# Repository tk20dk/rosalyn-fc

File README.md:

# rosalyn-fc
Rosalyn fligth controller

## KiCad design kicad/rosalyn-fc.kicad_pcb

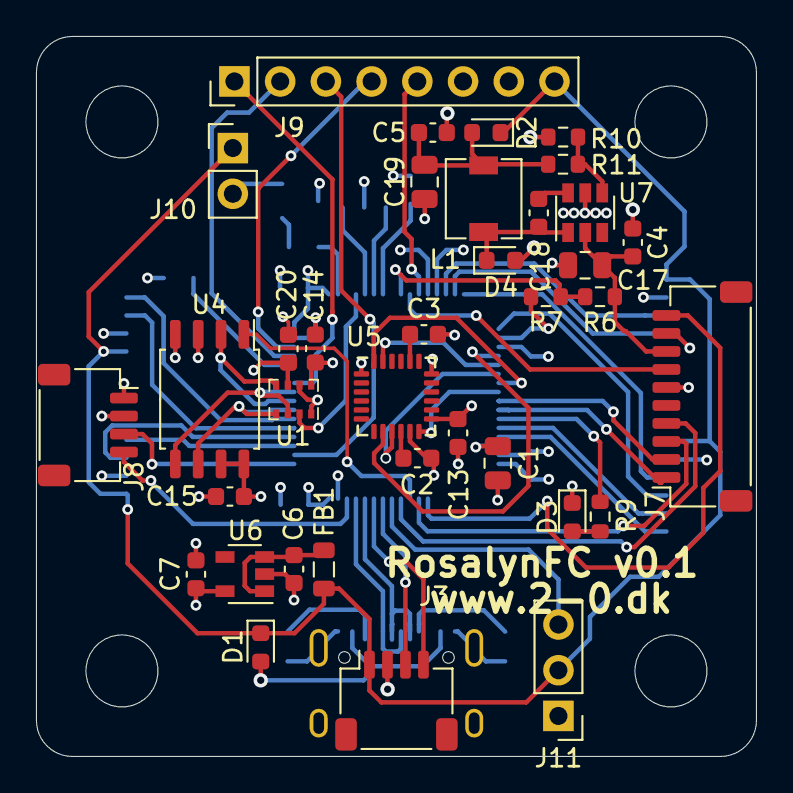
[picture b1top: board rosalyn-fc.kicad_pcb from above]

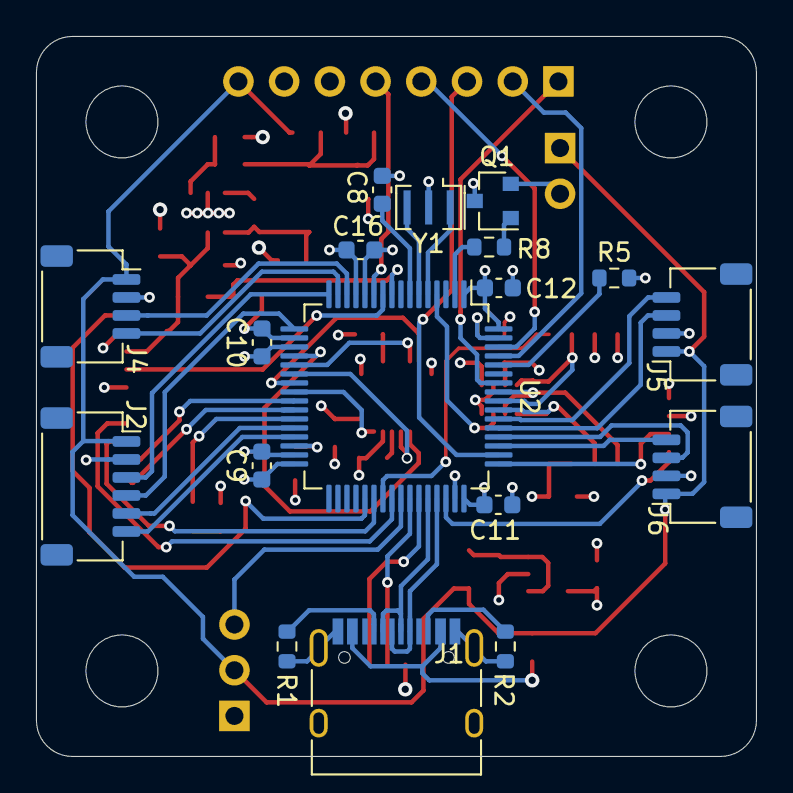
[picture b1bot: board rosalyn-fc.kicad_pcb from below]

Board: 4 copper layers, 40.0 x 40.0 mm, 58 parts (18 on the bottom side), 63 nets.

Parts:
C1: 4u7; C_0805_2012Metric
C2, C4, C5, C8, C9, C10, C11, C12, C13, C14, C15, C16, C20: 100n; C_0603_1608Metric
C3: 2.2n; C_0603_1608Metric
C6, C7: 1u; C_0603_1608Metric
C17: 10u; C_0805_2012Metric
C18: 22n; C_0603_1608Metric
C19: 22u; C_0805_2012Metric
D1, D2: D_Schottky; D_0603_1608Metric
D3: LED; LED_0603_1608Metric
D4: 1n5819; D_0603_1608Metric
FB1: Ferrite_Bead; L_0805_2012Metric
H1, H2, H3, H4: MountingHole; MountingHole_4mm
J1: USB-C; USB_C_Receptacle_HRO_TYPE-C-31-M-12
J2: GPS/MAG; JST_SH_SM06B-SRSS-TB_1x06-1MP_P1.00mm_Horizontal
J3: Terminal; JST_SH_SM04B-SRSS-TB_1x04-1MP_P1.00mm_Horizontal
J4: Satellite; JST_SH_SM04B-SRSS-TB_1x04-1MP_P1.00mm_Horizontal
J5: Serial1; JST_SH_SM04B-SRSS-TB_1x04-1MP_P1.00mm_Horizontal
J6: Serial2; JST_SH_SM04B-SRSS-TB_1x04-1MP_P1.00mm_Horizontal
J7: ESC; JST_SH_SM10B-SRSS-TB_1x10-1MP_P1.00mm_Horizontal
J8: SWD; JST_SH_SM04B-SRSS-TB_1x04-1MP_P1.00mm_Horizontal
J9: Expansion; PinHeader_1x08_P2.54mm_Vertical
J10: Buzzer; PinHeader_1x02_P2.54mm_Vertical
J11: PWM_LED; PinHeader_1x03_P2.54mm_Vertical
L1: 4,7u; L_4.1x4.1_H1.75
Q1: Q_NPN_BCE; SOT-23
R1, R2: 5k1; R_0603_1608Metric
R5: 100k; R_0603_1608Metric
R6: 10k; R_0603_1608Metric
R7: 1k; R_0603_1608Metric
R8, R9: R; R_0603_1608Metric
R10: 49,9k; R_0603_1608Metric
R11: 9,53k; R_0603_1608Metric
U1: BMP280; Bosch_LGA-8_2x2.5mm_P0.65mm_ClockwisePinNumbering
U2: STM32F722RETx; LQFP-64_10x10mm_P0.5mm
U4: W25Q128JVS; SOIC-8_5.275x5.275mm_P1.27mm
U5: MPU-6000; InvenSense_QFN-24_4x4mm_P0.5mm
U6: LP2985-3.3; SOT-23-5
U7: ACT4088; SOT-23-6
Y1: 8MHz; Resonator_SMD_muRata_CSTxExxV-3Pin_3.0x1.1mm

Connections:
+3V3: C7.1, C9.1, C10.1, C11.1, C12.1, C13.1, C14.1, C15.1, C16.1, C20.1, D3.1, J8.1, J9.7, U1.6, U1.8, U2.1, U2.13, U2.19, U2.32, U2.48, U2.64, U4.3, U4.7, U4.8, U5.13, U6.5
+5V: D1.1, D2.1, FB1.2, J2.1, J3.1, J4.1, J5.1, J6.1, J9.8, J10.1, J11.2
GND: C1.1, C2.2, C3.2, C4.2, C5.2, C6.1, C7.2, C8.2, C9.2, C10.2, C11.2, C12.2, C13.2, C14.2, C15.2, C16.2, C17.1, C19.2, C20.2, D4.2, J1.A1, J1.A12, J1.B1, J1.B12, J1.S1, J2.2, J3.2, J4.2, J5.2, J6.2, J7.6, J7.9, J8.2, J9.6, J11.1, Q1.3, R1.1, R2.1, R5.2, R7.2, R11.2, U1.1, U1.7, U2.12, U2.18, U2.31, U2.47, U2.63, U4.4, U5.1, U5.11, U5.18, U6.2, U7.5, Y1.2
unnamed: C1.2, U2.30
unnamed: C2.1, U5.10
unnamed: C3.1, U5.20
unnamed: C6.2, FB1.1, U6.1, U6.3
unnamed: C18.1, U7.6
unnamed: C18.2, D4.1, L1.2, U7.1
unnamed: C5.1, C19.1, D2.2, L1.1, R10.1
unnamed: D1.2, J1.A4, J1.A9, J1.B4, J1.B9
unnamed: D3.2, R9.2
unnamed: J1.A5, R1.2
unnamed: J1.B5, R2.2
unnamed: J10.2, Q1.2
unnamed: Q1.1, R8.1
unnamed: R10.2, R11.1, U7.4
unnamed: U2.5, Y1.1
unnamed: U2.6, Y1.3
baro_cs: U1.2, U2.4
beeper: R8.2, U2.2
boot0: R5.1, U2.60
camera: J9.4, U2.62
current_adc: J7.7, U2.10
flash_cs: U2.39, U4.1
gyro1_cs: U2.20, U5.8
gyro1_exti: U2.24, U5.12
i2c2_scl: J2.5, U2.28
i2c2_sda: J2.6, U2.29
led: J11.3, U2.41
led0: R9.1, U2.27
m1: J7.4, U2.40
m2: J7.3, U2.38
m3: J7.2, U2.25
m4: J7.1, U2.26
m5: J9.1, U2.58
m6: J9.2, U2.61
nrst: C8.1, U2.7
ppm: J9.3, U2.50
rssi_adc: J9.5, U2.11
spi1_miso: U2.22, U5.9
spi1_mosi: U2.23, U5.24
spi1_sck: U2.21, U5.23
spi3_miso: U1.5, U2.56, U4.2
spi3_mosi: U1.3, U2.57, U4.5
spi3_sck: U1.4, U2.55, U4.6
swclk: J8.3, U2.49
swdio: J8.4, U2.46
uart4_rx: J4.4, U2.15
uart4_tx: J4.3, U2.14
uart5_rx: J5.4, U2.54
uart5_tx: J5.3, U2.53
uart6_rxtx: J7.10, U2.37
usart1_rx: J3.4, U2.43
usart1_tx: J3.3, U2.42
usart2_rx: J2.4, U2.17
usart2_tx: J2.3, U2.16
usart3_rx: J6.4, U2.51
usart3_tx: J6.3, U2.52
usb_dm: J1.A7, J1.B7, U2.44
usb_dp: J1.A6, J1.B6, U2.45
vbat: C4.1, C17.2, J7.8, R6.1, U7.2
vbat_adc: R6.2, R7.1, U2.9

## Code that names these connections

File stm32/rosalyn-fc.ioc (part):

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Mcu.Name=STM32F722R(C-E)Tx
Mcu.Package=LQFP64
Mcu.UserName=STM32F722RETx
PA0-WKUP.Mode=Asynchronous
PA0-WKUP.Signal=UART4_TX
PA1.Mode=Asynchronous
PA1.Signal=UART4_RX
PA10.Mode=Asynchronous
PA10.Signal=USART1_RX
PA11.Mode=Device_Only
PA11.Signal=USB_OTG_FS_DM
PA12.Mode=Device_Only
PA12.Signal=USB_OTG_FS_DP
PA13.Mode=Serial_Wire
PA13.Signal=SYS_JTMS-SWDIO
PA14.Mode=Serial_Wire
PA14.Signal=SYS_JTCK-SWCLK
PA15.GPIOParameters=GPIO_Label
PA15.GPIO_Label=PPM
PA15.Signal=S_TIM2_CH1_ETR
PA2.Mode=Asynchronous
PA2.Signal=USART2_TX
PA3.Mode=Asynchronous
PA3.Signal=USART2_RX
PA4.GPIOParameters=PinState,GPIO_Label
PA4.GPIO_Label=GYRO1_NSS
PA4.PinState=GPIO_PIN_SET
PA4.Signal=GPIO_Output
PA5.Mode=Full_Duplex_Master
PA5.Signal=SPI1_SCK
PA6.GPIOParameters=GPIO_PuPd
PA6.GPIO_PuPd=GPIO_PULLUP
PA6.Mode=Full_Duplex_Master
PA6.Signal=SPI1_MISO
PA7.Mode=Full_Duplex_Master
PA7.Signal=SPI1_MOSI
PA8.GPIOParameters=GPIO_Label
PA8.GPIO_Label=LED
PA8.Signal=S_TIM1_CH1
PA9.Mode=Asynchronous
PA9.Signal=USART1_TX
PB0.GPIOParameters=GPIO_Label
PB0.GPIO_Label=M3
PB0.Signal=S_TIM3_CH3
PB1.GPIOParameters=GPIO_Label
PB1.GPIO_Label=M4
PB1.Signal=S_TIM3_CH4
PB10.Mode=I2C
PB10.Signal=I2C2_SCL
PB11.Mode=I2C
PB11.Signal=I2C2_SDA
PB12.GPIOParameters=PinState,GPIO_Label
PB12.GPIO_Label=SPI2_NSS
PB12.PinState=GPIO_PIN_SET
PB12.Signal=GPIO_Output
PB13.Mode=Full_Duplex_Master
PB13.Signal=SPI2_SCK
PB14.GPIOParameters=GPIO_PuPd
PB14.GPIO_PuPd=GPIO_PULLUP
PB14.Mode=Full_Duplex_Master
PB14.Signal=SPI2_MISO
PB15.Mode=Full_Duplex_Master
PB15.Signal=SPI2_MOSI
PB2.GPIOParameters=PinState,GPIO_Label
PB2.GPIO_Label=LED0
PB2.PinState=GPIO_PIN_SET
PB2.Signal=GPIO_Output
PB3.Mode=Full_Duplex_Master
PB3.Signal=SPI3_SCK
PB4.GPIOParameters=GPIO_PuPd
PB4.GPIO_PuPd=GPIO_PULLUP
PB4.Mode=Full_Duplex_Master
PB4.Signal=SPI3_MISO
PB5.Mode=Full_Duplex_Master
PB5.Signal=SPI3_MOSI
PB6.GPIOParameters=GPIO_Label
PB6.GPIO_Label=M5
PB6.Signal=S_TIM4_CH1
PB8.GPIOParameters=GPIO_Label
PB8.GPIO_Label=M6
PB8.Signal=S_TIM4_CH3
PB9.GPIOParameters=GPIO_Label
PB9.GPIO_Label=CAMERA_CONTROL
PB9.Signal=S_TIM11_CH1
PC1.GPIOParameters=GPIO_Label
PC1.GPIO_Label=VBAT_ADC
PC1.Signal=ADCx_IN11
PC10.Mode=Asynchronous
PC10.Signal=USART3_TX
PC11.Mode=Asynchronous
PC11.Signal=USART3_RX
PC12.Mode=Asynchronous
PC12.Signal=UART5_TX
PC13.GPIOParameters=GPIO_Label
PC13.GPIO_Label=BEEPER
PC13.Signal=GPIO_Output
PC15-OSC32_OUT.GPIOParameters=PinState,GPIO_Label
PC15-OSC32_OUT.GPIO_Label=BARO_NSS
PC15-OSC32_OUT.PinState=GPIO_PIN_SET
PC15-OSC32_OUT.Signal=GPIO_Output
PC2.GPIOParameters=GPIO_Label
PC2.GPIO_Label=CURRENT_ADC
PC2.Signal=ADCx_IN12
PC3.GPIOParameters=GPIO_Label
PC3.GPIO_Label=RSSI_ADC
PC3.Signal=ADCx_IN13
PC4.GPIOParameters=GPIO_Label
PC4.GPIO_Label=GYRO1_EXTI
PC4.Signal=GPXTI4
PC6.Mode=Half_duplex(single_wire_mode)
PC6.Signal=USART6_TX
PC7.GPIOParameters=GPIO_Label
PC7.GPIO_Label=M2
PC7.Signal=S_TIM8_CH2
PC8.GPIOParameters=PinState,GPIO_Label
PC8.GPIO_Label=FLASH_CS
PC8.PinState=GPIO_PIN_SET
PC8.Signal=GPIO_Output
PC9.GPIOParameters=GPIO_Label
PC9.GPIO_Label=M1
PC9.Signal=S_TIM8_CH4
PD2.Mode=Asynchronous
PD2.Signal=UART5_RX
PH0-OSC_IN.Mode=HSE-External-Oscillator
PH0-OSC_IN.Signal=RCC_OSC_IN
PH1-OSC_OUT.Mode=HSE-External-Oscillator
PH1-OSC_OUT.Signal=RCC_OSC_OUT
RCC.HSE_VALUE=8000000
RCC.SYSCLKFreq_VALUE=216000000
RCC.SYSCLKSource=RCC_SYSCLKSOURCE_PLLCLK
board=custom

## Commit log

2020-11-22 ready for review
2020-11-23 rosalyn-fc v0.1
2020-12-16 cpu running at 216MHz
2020-12-17 added mpu6000 driver
2020-12-17 updated mpu6000 driver
2020-12-18 mpu6000 is working
2020-12-18 bmp280 is working
2020-12-18 W25Q128 is working
2020-12-18 updated schematic lable names
2020-12-31 added pdf documents
2021-01-01 added comment about DAC camera control
2021-01-03 added video support
